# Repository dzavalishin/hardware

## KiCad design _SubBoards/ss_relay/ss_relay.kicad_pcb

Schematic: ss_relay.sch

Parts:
C1, C2, C3: 0,1; C_1206_HandSoldering
C4: 0,1 400v; C_Rect_L10.3mm_W5.0mm_P7.50mm_MKS4
D1, D7: MB6S; Diode_Bridge_TO-269AA
D2, D3: LED; LED_D3.0mm
D4: 7,5v 1500a; D_DO-201AD_P5.08mm_Vertical_KathodeUp
D5, D8: 5v6; D_1206
D6: RL206; D_DO-15_P5.08mm_Vertical_AnodeUp
F1: 0,5A; Fuseholder5x20_horiz_open_inline_Type-I
J1: DC Load; TerminalBlock_Pheonix_MPT-2.54mm_2pol
J2: AC220; TerminalBlock_Pheonix_MPT-2.54mm_2pol
P1: CONN_01X02; Pin_Header_Straight_1x02_Pitch2.54mm
Q1: IRF730; TO-220-3_Vertical
R1, R2: 560; R_1206_HandSoldering
R3, R4: 1k; R_1206_HandSoldering
R5, R6: 470k 1W; R_Axial_DIN0617_L17.0mm_D6.0mm_P20.32mm_Horizontal
R7: 56; R_Axial_DIN0617_L17.0mm_D6.0mm_P20.32mm_Horizontal
RV1: 14K391; RV_Disc_D21.5_W4.3_P10
U1: PC817; SOP-4_3.8x4.1mm_Pitch2.54mm

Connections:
unnamed: C1.1, D2.2, D8.1, R1.1, R4.2
unnamed: C1.2, D8.2, R2.2, R3.2, U1.2
unnamed: C2.1, D4.1, Q1.1 (G), R5.2, U1.4
unnamed: C2.2, D4.2, D7.2 (-), Q1.3 (S), U1.3
unnamed: C3.1, C4.1, D3.2, D5.1, D6.1, D7.1 (+), J1.2, R5.1
unnamed: C3.2, D3.1, D5.2, R6.1
unnamed: C4.2, R7.1
unnamed: D1.1 (+), R1.2
unnamed: D1.2 (-), R2.1
unnamed: D1.3, P1.1
unnamed: D1.4, P1.2
unnamed: D2.1, R3.1
unnamed: D6.2, J1.1, Q1.2 (D), R6.2, R7.2
unnamed: D7.3, J2.1, RV1.2
unnamed: D7.4, F1.2, RV1.1
unnamed: F1.1, J2.2
unnamed: R4.1, U1.1

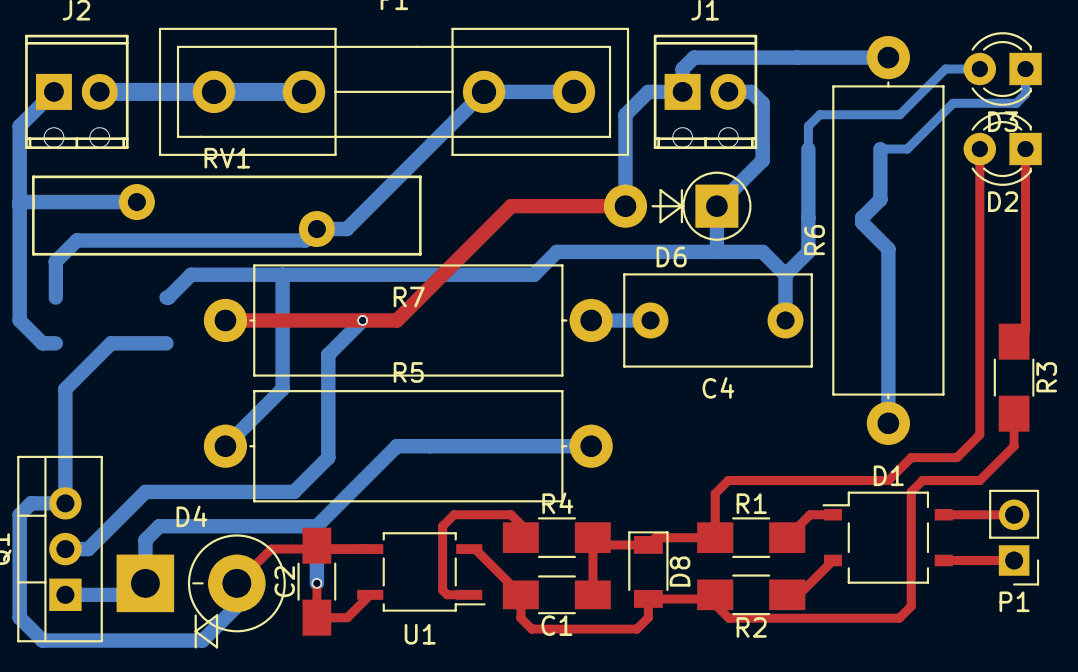
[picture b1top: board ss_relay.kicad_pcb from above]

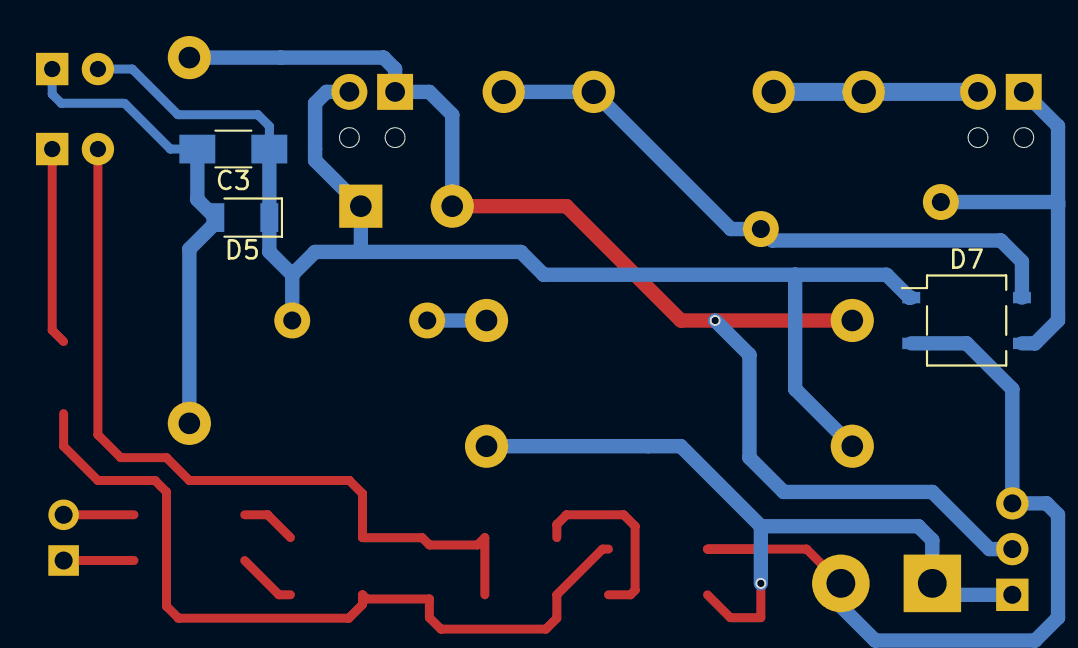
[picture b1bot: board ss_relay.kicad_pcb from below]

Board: 2 copper layers, 26 parts (3 on the bottom side), 17 nets.

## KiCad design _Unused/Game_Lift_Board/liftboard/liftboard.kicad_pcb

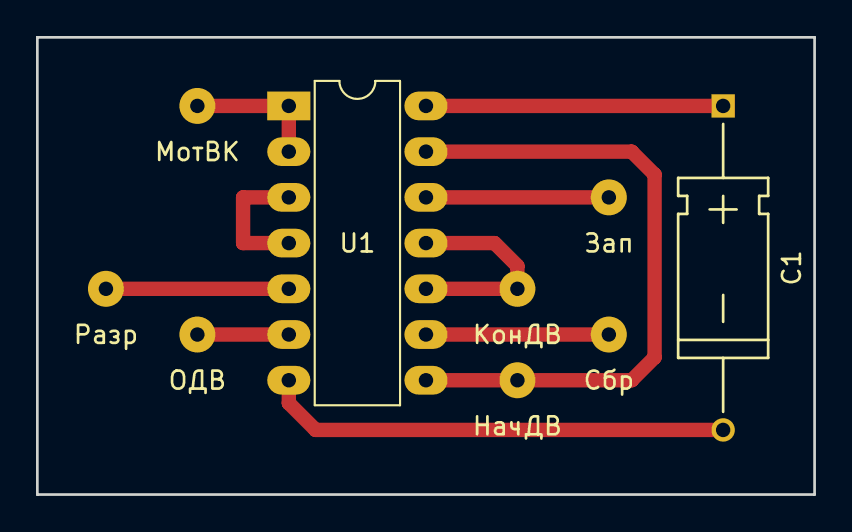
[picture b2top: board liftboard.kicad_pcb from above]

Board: 2 copper layers, 43.2 x 25.4 mm, 9 parts (0 on the bottom side), 10 nets.

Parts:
C1: C; C_Axial_D5_L11_P18
J1: МотВК; SolderWirePad_1x01_Drill0.8mm
J2: ОДВ; SolderWirePad_1x01_Drill0.8mm
J3: Разр; SolderWirePad_1x01_Drill0.8mm
J4: Зап; SolderWirePad_1x01_Drill0.8mm
J5: КонДВ; SolderWirePad_1x01_Drill0.8mm
J6: Сбр; SolderWirePad_1x01_Drill0.8mm
J7: НачДВ; SolderWirePad_1x01_Drill0.8mm
U1: 7400; DIP-14_W7.62mm_LongPads

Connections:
unnamed: C1.1, U1.14
unnamed: C1.2, U1.7
unnamed: J1.1, U1.1, U1.2
unnamed: J2.1, U1.6
unnamed: J3.1, U1.5
unnamed: J4.1, U1.12
unnamed: J5.1, U1.10, U1.11
unnamed: J6.1, U1.9
unnamed: J7.1, U1.8, U1.13
unnamed: U1.3, U1.4

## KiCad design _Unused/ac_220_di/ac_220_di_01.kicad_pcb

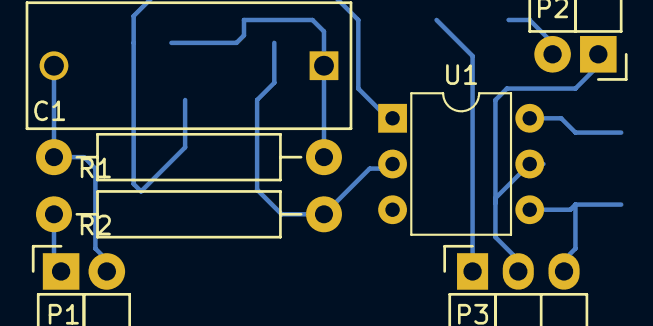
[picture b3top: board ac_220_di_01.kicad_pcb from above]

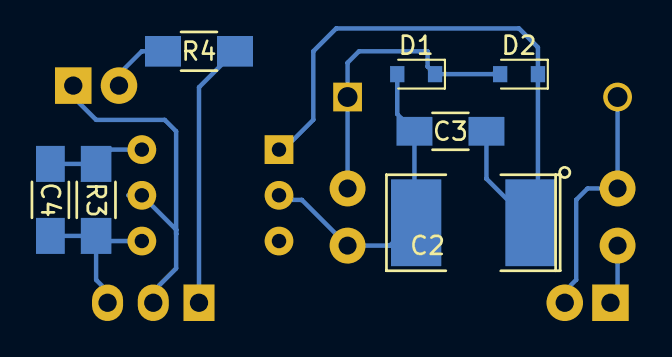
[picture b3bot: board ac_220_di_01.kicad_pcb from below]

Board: 2 copper layers, 14 parts (7 on the bottom side), 10 nets.

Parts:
C1: 0.15uF; C_Rect_L18_W7_P15
C2: 10,0; SMD-2112_Pol
C3: 0,1; C_1206_HandSoldering
C4: 100pf; C_1206_HandSoldering
D1, D2: 4448; D_0805
P1: In; Socket_Strip_Angled_1x02
P2: Led; Socket_Strip_Angled_1x02
P3: Out; Socket_Strip_Angled_1x03
R1: 3m; Resistor_Horizontal_RM15mm
R2: 10k 1W; Resistor_Horizontal_RM15mm
R3: 470k; R_1206_HandSoldering
R4: 4,7k (10ma) or 12k (2ma); R_1206_HandSoldering
U1: 4N35; DIP-6_W7.62mm

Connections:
unnamed: C1.1, D1.1, D2.2, R1.1
unnamed: C1.2, P1.2, R1.2
unnamed: C2.1, C3.1, D2.1, U1.1
unnamed: C2.2, C3.2, D1.2, R2.1, U1.2
unnamed: C4.1, R3.2, U1.6
unnamed: C4.2, P3.3, R3.1, U1.4
unnamed: P1.1, R2.2
unnamed: P2.1, P3.2, U1.5
unnamed: P2.2, R4.1
unnamed: P3.1, R4.2

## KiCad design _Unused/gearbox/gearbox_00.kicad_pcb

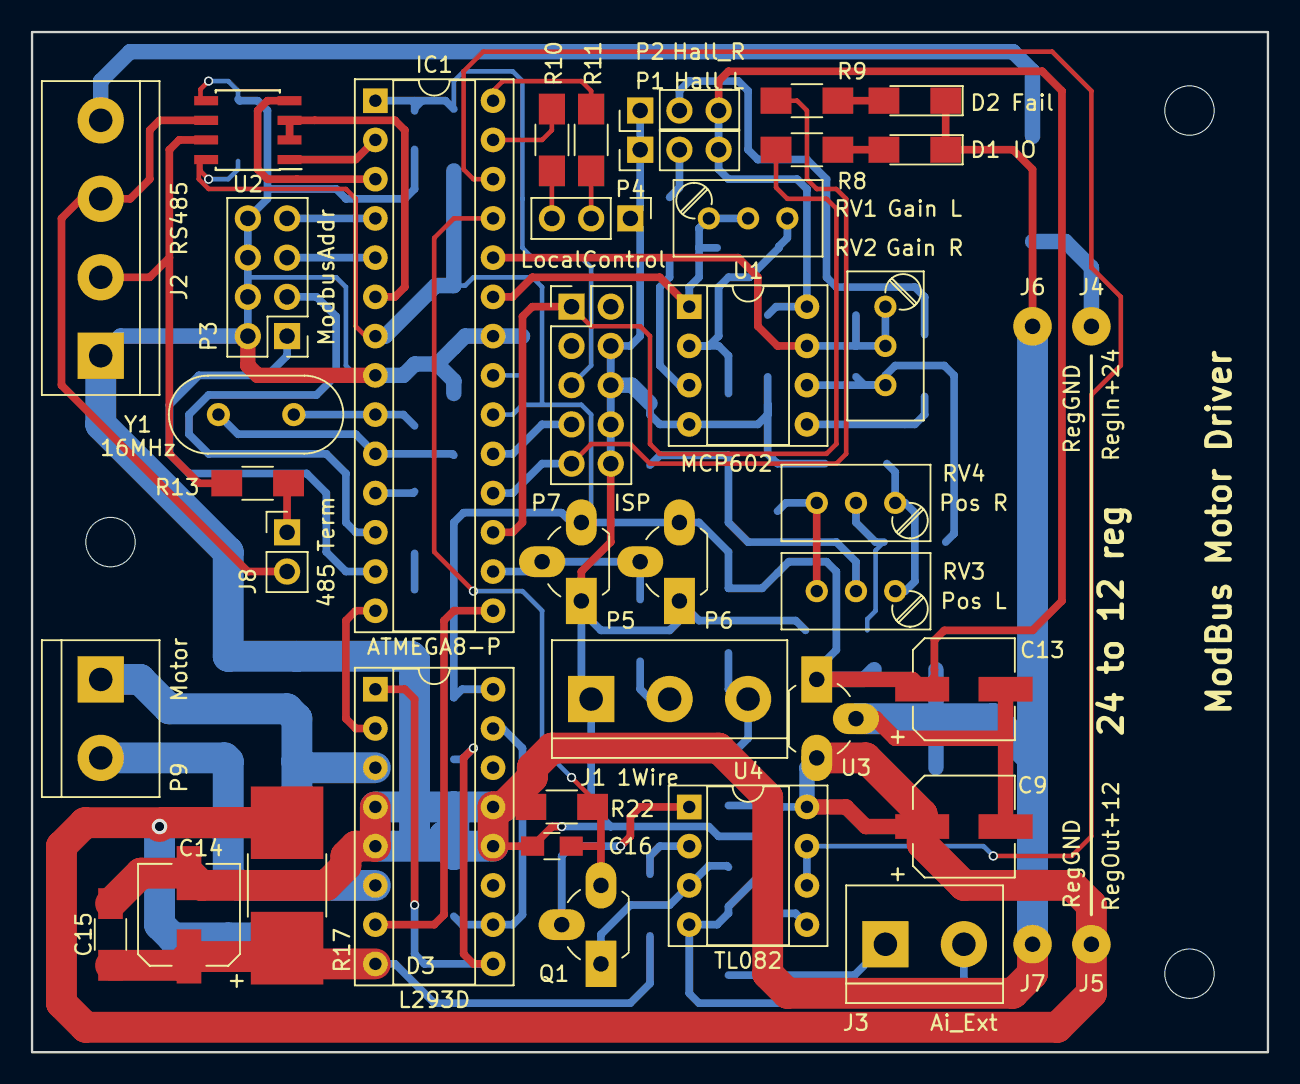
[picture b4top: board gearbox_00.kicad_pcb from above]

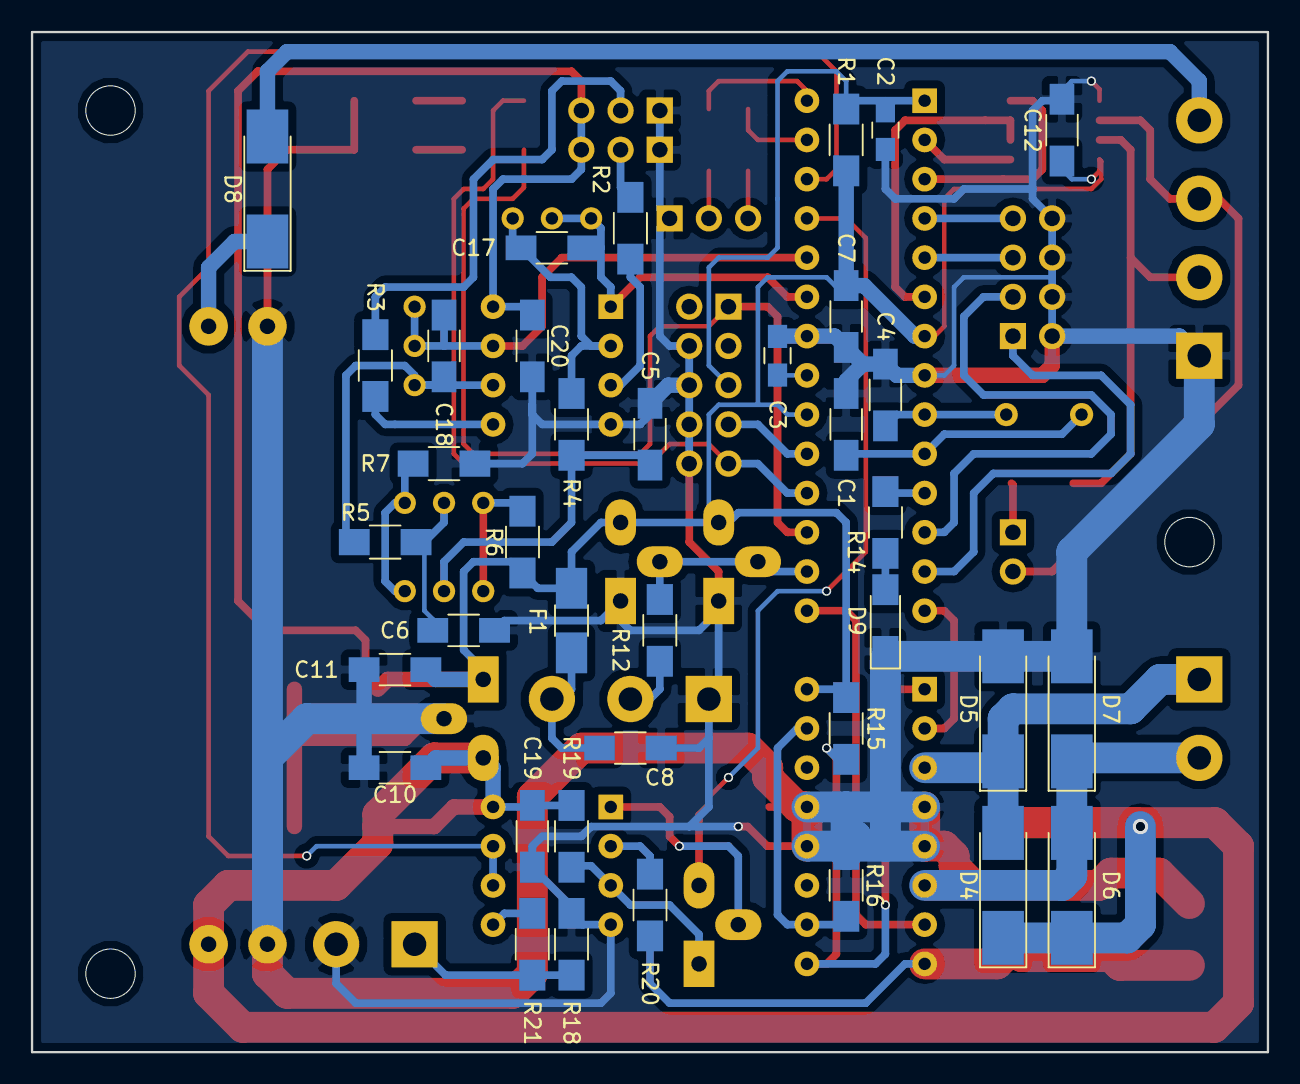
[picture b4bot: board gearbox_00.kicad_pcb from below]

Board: 2 copper layers, 80.0 x 66.0 mm, 82 parts (37 on the bottom side), 59 nets.

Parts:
C1, C4: 18pF; C_1206_HandSoldering
C2, C3, C16: 1,0; C_0805_HandSoldering
C5, C6, C7, C8, C10, C11, C12, C15, C19, C20: 0,1; C_1206_HandSoldering
C9: 220,0; CP_Elec_6.3x5.3
C13: 22,0; CP_Elec_6.3x5.3
C14: 47,0; CP_Elec_6.3x5.3
C17, C18: 0,01; C_1206_HandSoldering
D1: IO; LED_1206_HandSoldering
D2: Fail; LED_1206_HandSoldering
D3: L293D; DIP-16_W7.62mm_Socket
D4, D5, D6, D7, D8: SS34; D_MELF_Handsoldering
D9: Debug; LED_1206_HandSoldering
F1: 0,1a; Fuse_SMD1206_HandSoldering
IC1: ATMEGA8-P; DIP-28_W7.62mm_Socket
J1: 1Wire; TerminalBlock_bornier-3_P5.08mm
J2: RS485; TerminalBlock_bornier-4_P5.08mm
J3: Ai_Ext; TerminalBlock_bornier-2_P5.08mm
J4: RegIn+24; SolderWirePad_single_1mmDrill
J5: RegOut+12; SolderWirePad_single_1mmDrill
J6, J7: RegGND; SolderWirePad_single_1mmDrill
J8: 485 Term; Pin_Header_Straight_1x02_Pitch2.54mm
P1: Hall_L; Pin_Header_Straight_1x03_Pitch2.54mm
P2: Hall_R; Pin_Header_Straight_1x03_Pitch2.54mm
P3: ModbusAddr; Pin_Header_Straight_2x04_Pitch2.54mm
P4: LocalControl; Pin_Header_Straight_1x03_Pitch2.54mm
P5: DS2401; TO-92_Rugged
P6: DS18B20; TO-92_Rugged
P7: ISP; Pin_Header_Straight_2x05_Pitch2.54mm
P9: Motor; TerminalBlock_bornier-2_P5.08mm
Q1: 2N3904; TO-92_Rugged
R1, R6, R7, R10, R11, R21: 1k; R_1206_HandSoldering
R2, R3, R15, R16: 10k; R_1206_HandSoldering
R4, R5: 22k; R_1206_HandSoldering
R8, R9, R14: 2,2k; R_1206_HandSoldering
R12: 100; R_1206_HandSoldering
R13: 47; R_1206_HandSoldering
R17: 0,2; R_2816_HandSoldering
R18: 1M; R_1206_HandSoldering
R19, R20: 200; R_1206_HandSoldering
R22: 2k; R_1206_HandSoldering
RV1, RV2: 22k; Potentiometer_Trimmer_Bourns_3296W
RV3, RV4: 1k; Potentiometer_Trimmer_Bourns_3296W
U1: MCP602; DIP-8_W7.62mm_Socket
U2: MAX485; SOIC-8_3.9x4.9mm_Pitch1.27mm
U3: LM78L05ACZ; TO-92_Rugged
U4: TL082; DIP-8_W7.62mm_Socket
Y1: 16MHz; Crystal_HC49-U_Vertical
hole: MountingHole_3.2mm_M3
hole#2, hole#3: MountingHole_3.2mm_M3

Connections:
+5V: C7.1, C11.2, C12.1, C13.1, C20.1, D3.16, F1.2, IC1.7, IC1.20, P1.3, P2.3, P5.3, P6.3, R1.1, R6.1, R15.2, U1.8, U2.8, U3.1
+12V: C9.1, C10.1, C19.1, D4.1, D6.1, J5.1, R17.1, R19.2, U3.3, U4.8
+24V: D8.1, J4.1
/1Wire: IC1.16, P5.2, P6.2, R12.2
/Ai_Ext: IC1.26, U4.6, U4.7
/Ai_Hall_A: C17.1, IC1.23, RV1.1, RV1.2, U1.1
/Ai_Hall_B: C18.1, IC1.24, RV2.1, RV2.2, U1.7
/Ai_I_Sense: C16.1, IC1.25, Q1.3, R22.1
/Fail_Led: IC1.18, P7.9, R9.2
/IO_Led: IC1.17, P7.1, R8.2
/LocalClose: IC1.28, R11.2
/LocalOpen: IC1.27, R10.2
/OutA: D3.2, IC1.14
/OutB: D3.7, IC1.15
/Reset: C2.1, IC1.1, P7.5, R1.2
/Rx: IC1.2, U2.1
/SCK: IC1.19, P7.7
/Tx: IC1.3, U2.4
/TxE: IC1.6, U2.2, U2.3
GND: C1.2, C2.2, C3.2, C4.2, C5.2, C6.2, C7.2, C8.2, C9.2, C10.2, C11.1, C12.2, C13.2, C14.2, C15.2, C16.2, C19.2, C20.2, D1.1, D2.1, D3.4, D3.5, D3.12, D3.13, D5.2, D7.2, D9.1, IC1.8, IC1.22, J1.1, J2.1, J3.2, J6.1, J7.1, P1.1, P2.1, P3.2, P3.4, P3.6, P3.8, P4.1, P5.1, P6.1, P7.4, P7.6, P7.8, P7.10, R7.2, R16.1, R18.1, R22.2, U1.4, U2.5, U3.2, U4.4
unnamed: C1.1, IC1.10, Y1.1
unnamed: C3.1, IC1.21
unnamed: C4.1, IC1.9, Y1.2
unnamed: C5.1, R4.2, RV3.2
unnamed: C6.1, R5.2, RV4.2
unnamed: C8.1, F1.1, J1.3
unnamed: C14.1, C15.1, D3.8, R17.2, R20.2
unnamed: C17.2, R4.1, RV1.3, U1.2
unnamed: C18.2, R5.1, RV2.3, U1.6
unnamed: D1.2, R8.1
unnamed: D2.2, R9.1
unnamed: D3.1, D3.9, R15.1
unnamed: D3.3, D4.2, D5.1, P9.1
unnamed: D3.6, D6.2, D7.1, P9.2
unnamed: D3.10, D3.15, R16.2
unnamed: D8.2, J2.4
unnamed: D9.2, R14.1
unnamed: IC1.4, P3.7
unnamed: IC1.5, P3.5
unnamed: IC1.11, R14.2
unnamed: IC1.12, P3.3
unnamed: IC1.13, P3.1
unnamed: J1.2, R12.1
unnamed: J2.2, R13.2, U2.7
unnamed: J2.3, J8.2, U2.6
unnamed: J3.1, R18.2, R21.2
unnamed: J8.1, R13.1
unnamed: P1.2, R2.2
unnamed: P2.2, R3.2
unnamed: P4.2, R11.1
unnamed: P4.3, R10.1
unnamed: Q1.1, R19.1, U4.3
unnamed: Q1.2, U4.1
unnamed: R2.1, U1.3
unnamed: R3.1, U1.5
unnamed: R6.2, RV3.3, RV4.3
unnamed: R7.1, RV3.1, RV4.1
unnamed: R20.1, U4.2
unnamed: R21.1, U4.5

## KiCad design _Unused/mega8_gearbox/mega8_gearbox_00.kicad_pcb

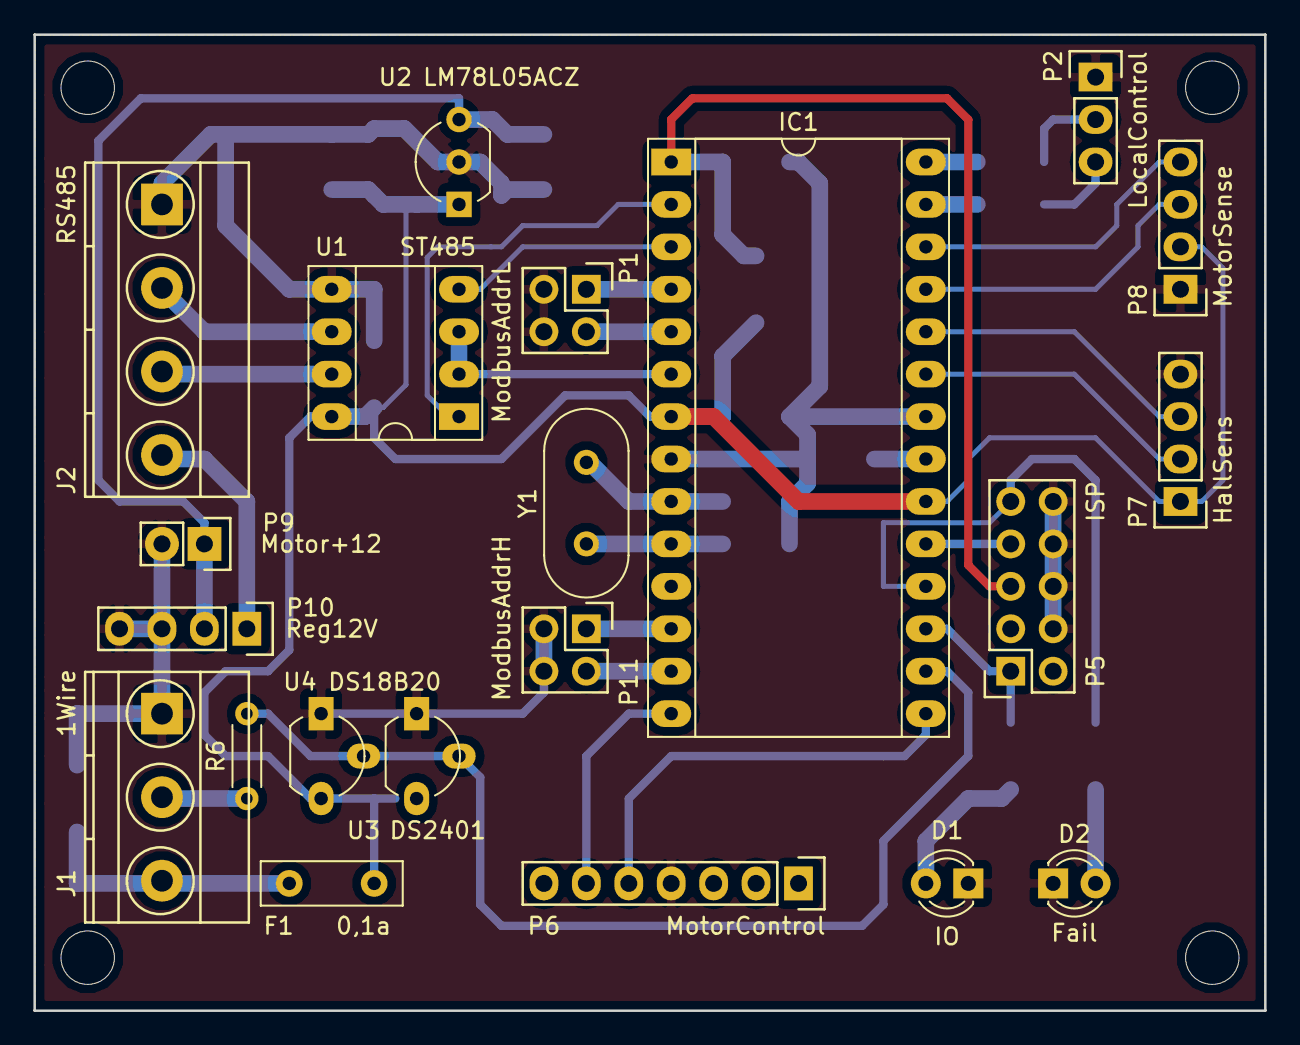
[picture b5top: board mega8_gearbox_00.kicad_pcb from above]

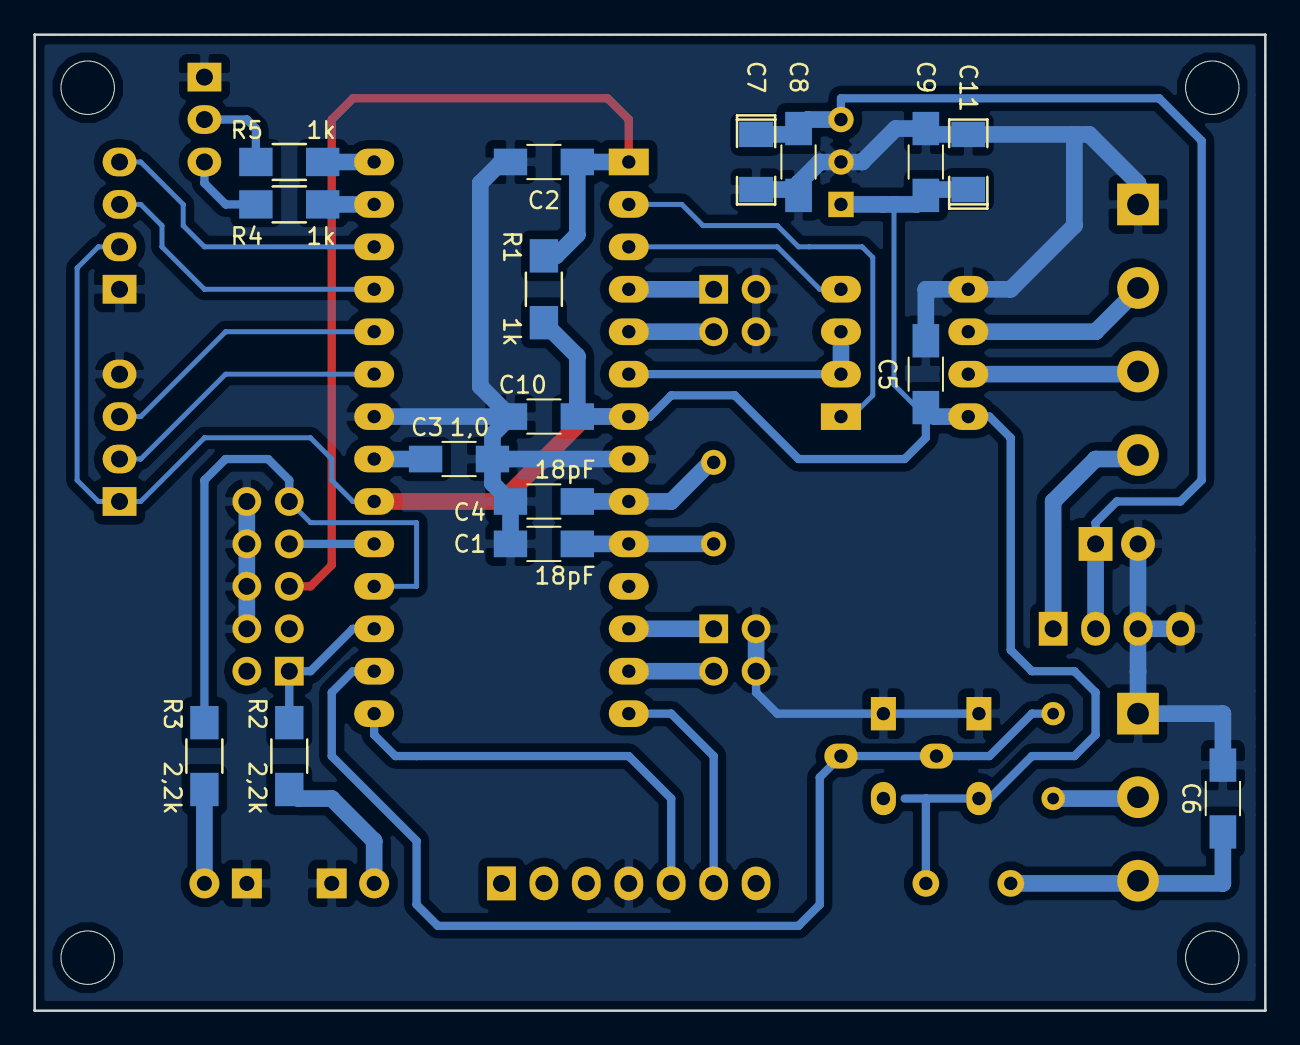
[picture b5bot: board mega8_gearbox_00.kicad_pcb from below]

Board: 2 copper layers, 73.7 x 58.4 mm, 41 parts (16 on the bottom side), 35 nets.

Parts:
C1, C4: 18pF; C_1206_HandSoldering
C2, C3: 1,0; C_1206_HandSoldering
C5, C6, C8, C9, C10: 0,1; C_1206_HandSoldering
C7, C11: 10,0; SMD-1206_Pol
D1: IO; LED_D3.0mm
D2: Fail; LED_D3.0mm
F1: 0,1a; R_Box_L8.4mm_W2.5mm_P5.08mm
IC1: ATMEGA8-P; DIP-28_W15.24mm_Socket_LongPads
J1: 1Wire; TerminalBlock_Pheonix_MKDS1.5-3pol
J2: RS485; TerminalBlock_Pheonix_MKDS1.5-4pol
P1: ModbusAddrL; Socket_Strip_Straight_2x02
P2: LocalControl; Socket_Strip_Straight_1x03
P5: ISP; Socket_Strip_Straight_2x05
P6: MotorControl; Socket_Strip_Straight_1x07
P7: HallSens; Socket_Strip_Straight_1x04
P8: MotorSense; Socket_Strip_Straight_1x04
P9: Motor+12; Socket_Strip_Straight_1x02
P10: Reg12V; Socket_Strip_Straight_1x04
P11: ModbusAddrH; Socket_Strip_Straight_2x02
R1, R4, R5: 1k; R_1206_HandSoldering
R2, R3: 2,2k; R_1206_HandSoldering
R6: 100; R_Axial_DIN0204_L3.6mm_D1.6mm_P5.08mm_Horizontal
U1: ST485; DIP-8_W7.62mm_Socket_LongPads
U2: LM78L05ACZ; TO-92_Inline_Wide
U3: DS2401; TO-92_Molded_Wide_Oval
U4: DS18B20; TO-92_Molded_Wide_Oval
Y1: 16MHz; Crystal_HC49-U_Vertical
hole: MountingHole_3.2mm_M3
hole#2, hole#3, hole#4: MountingHole_3.2mm_M3

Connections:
+5V: C5.1, C9.2, C10.1, C11.1, F1.2, IC1.7, IC1.20, P7.1, P8.2, R1.1, U1.8, U2.1, U4.3
+12V: C7.1, C8.1, P9.1, P10.2, U2.3
+24V: J2.4, P10.1
/1Wire: IC1.16, R6.2, U3.2, U4.2
/Ai_Ext: IC1.26, P8.4
/Ai_Hall_A: IC1.23, P7.2
/Ai_Hall_B: IC1.24, P7.3
/Ai_I_Sense: IC1.25, P8.3
/Fail_Led: IC1.18, P5.9, R3.2
/IO_Led: IC1.17, P5.1, R2.2
/LocalClose: IC1.28, R5.2
/LocalOpen: IC1.27, R4.2
/OutA: IC1.14, P6.6
/OutB: IC1.15, P6.5
/Reset: C2.1, IC1.1, P5.5, R1.2
/Rx: IC1.2, U1.1
/SCK: IC1.19, P5.7
/Tx: IC1.3, U1.4
/TxE: IC1.6, U1.2, U1.3
GND: C1.2, C2.2, C3.2, C4.2, C5.2, C6.2, C7.2, C8.2, C9.1, C10.2, C11.2, D1.1, D2.1, IC1.8, IC1.22, J1.1, J2.1, P1.2, P1.4, P2.1, P5.4, P5.6, P5.8, P5.10, P6.4, P7.4, P8.1, P9.2, P10.3, P10.4, P11.2, P11.4, U1.5, U2.2, U3.1, U4.1
unnamed: C1.1, IC1.10, Y1.1
unnamed: C3.1, IC1.21
unnamed: C4.1, IC1.9, Y1.2
unnamed: C6.1, F1.1, J1.3
unnamed: D1.2, R2.1
unnamed: D2.2, R3.1
unnamed: IC1.4, P1.1
unnamed: IC1.5, P1.3
unnamed: IC1.12, P11.1
unnamed: IC1.13, P11.3
unnamed: J1.2, R6.1
unnamed: J2.2, U1.6
unnamed: J2.3, U1.7
unnamed: P2.2, R5.1
unnamed: P2.3, R4.1

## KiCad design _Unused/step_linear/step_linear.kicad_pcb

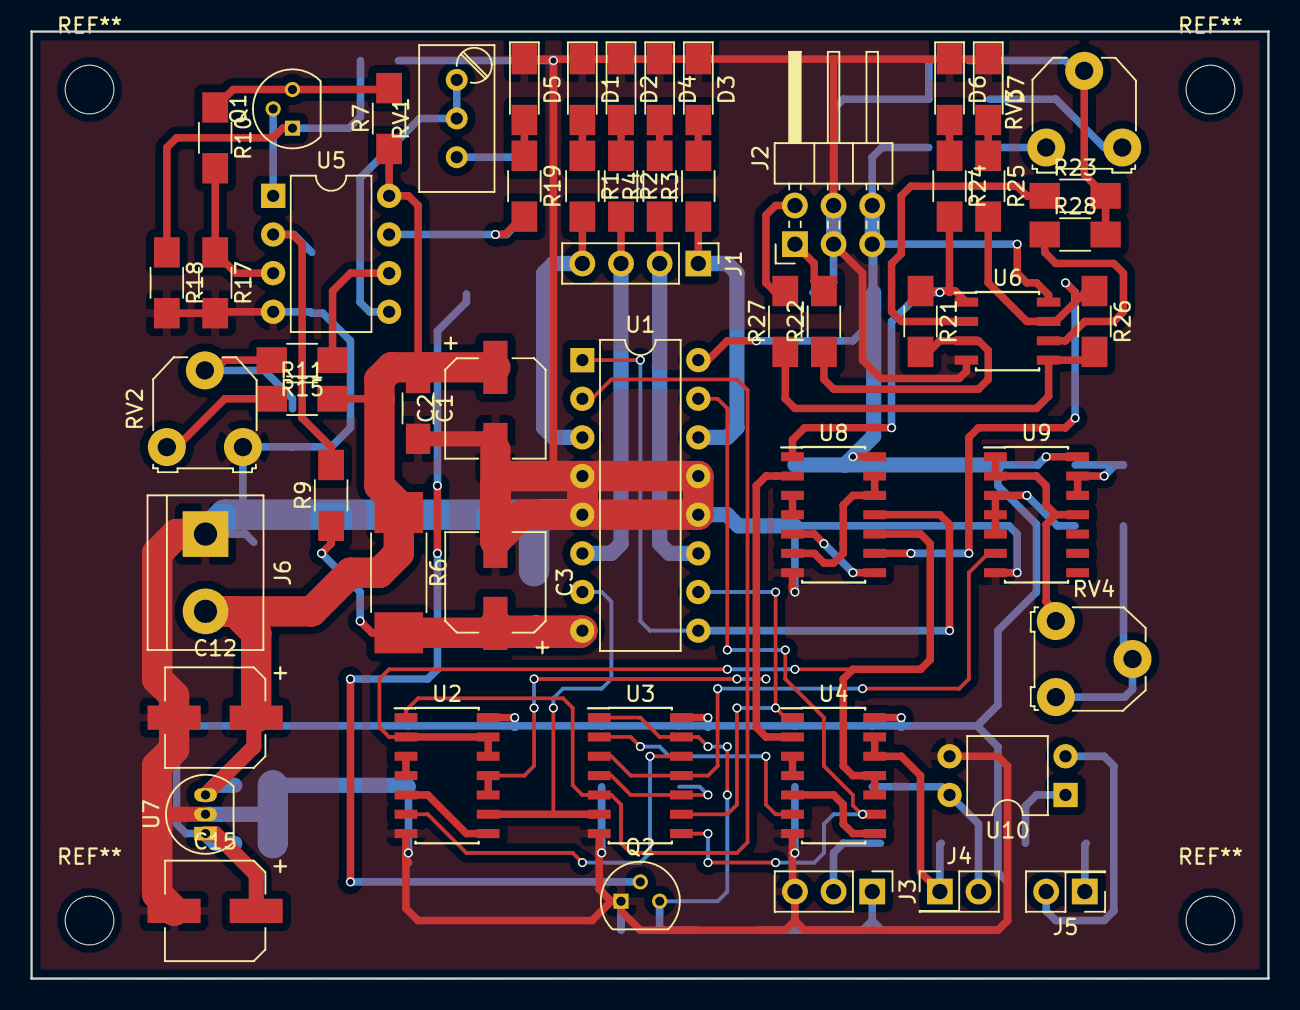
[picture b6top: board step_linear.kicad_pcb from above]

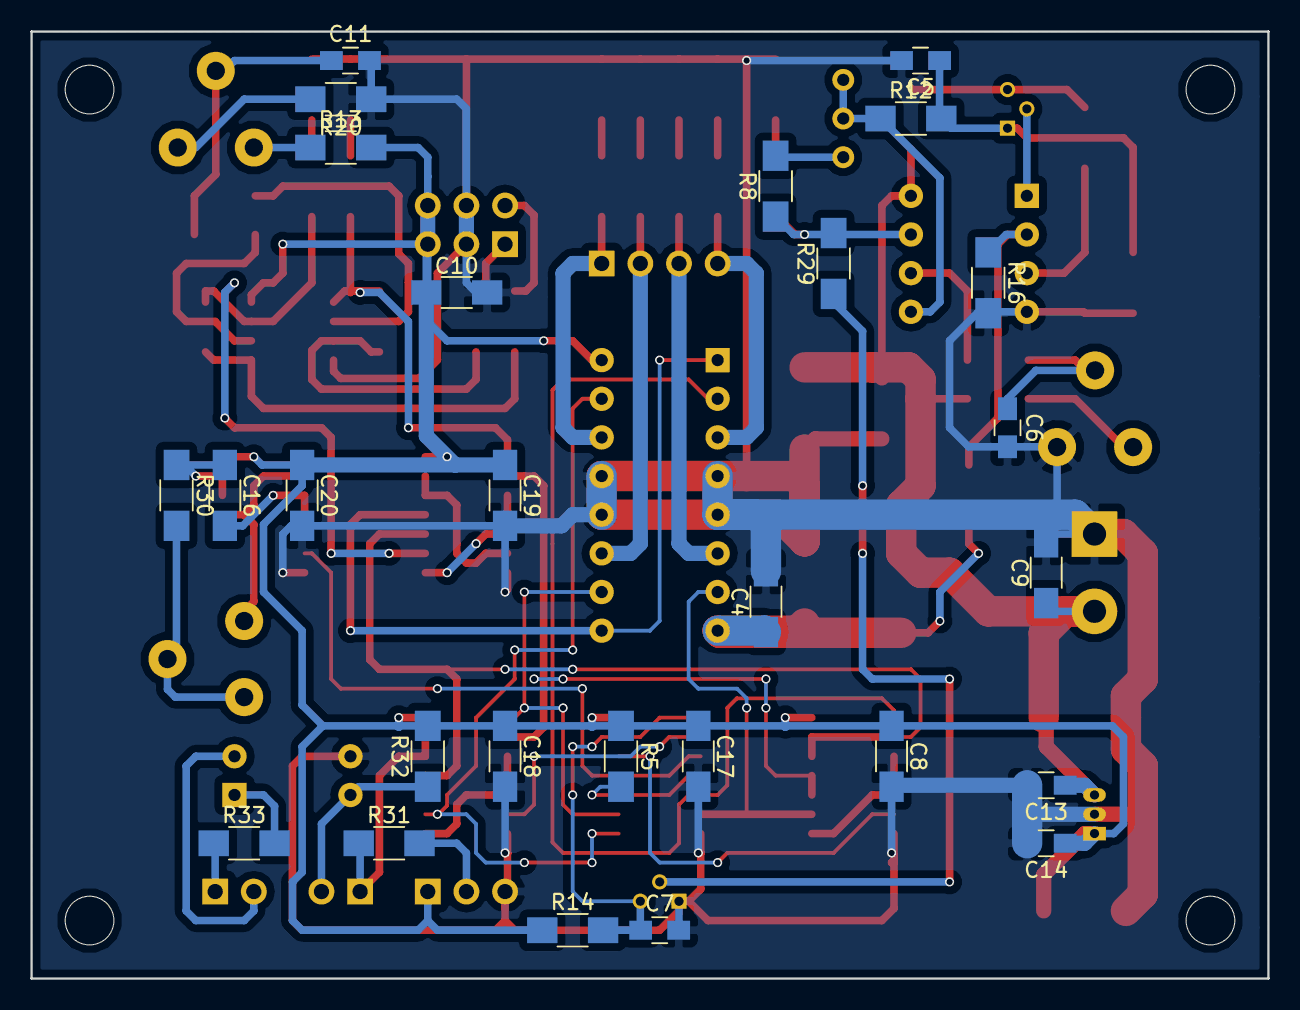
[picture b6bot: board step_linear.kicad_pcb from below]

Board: 2 copper layers, 81.3 x 62.2 mm, 82 parts (27 on the bottom side), 67 nets.

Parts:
C1, C4, C8, C9, C10, C17, C18, C19, C20: 0,1; C_1206_HandSoldering
C2, C3, C12: 47,0; CP_Elec_6.3x5.3
C5, C6, C7, C11: 1,0; C_0805_HandSoldering
C13, C14: 0,33; C_0805_HandSoldering
C15: 100,0; CP_Elec_6.3x5.7
C16: 0,15; C_1206_HandSoldering
D1, D2, D3, D4, D5, D6, D7: LED; LED_1206_HandSoldering
J1: Motor; Pin_Header_Straight_1x04_Pitch2.54mm
J2: Hall; Pin_Header_Angled_2x03_Pitch2.54mm
J3: Direction; Pin_Header_Straight_1x03_Pitch2.54mm
J4: Opto; Pin_Header_Straight_2x01_Pitch2.54mm
J5: Dir; Pin_Header_Straight_2x01_Pitch2.54mm
J6: +12; TerminalBlock_bornier-2_P5.08mm
Q1, Q2: 2N3904; TO-92_Molded_Narrow
R1, R2, R3, R4, R19, R24, R25: 560; R_1206_HandSoldering
R5, R9, R10, R12, R14, R15, R16, R17, R29: 10k; R_1206_HandSoldering
R6: 0,2 2W 1%; R_2512_HandSoldering
R7: 200 1%; R_1206_HandSoldering
R8: 1,5m; R_1206_HandSoldering
R11: 9,1k; R_1206_HandSoldering
R13, R20, R22, R23, R27, R28, R32, R33: 1k; R_1206_HandSoldering
R18: 2k 1%; R_1206_HandSoldering
R21, R26: 220k; R_1206_HandSoldering
R30: 3,3k; R_1206_HandSoldering
R31: 120; R_1206_HandSoldering
RV1: 1m; Potentiometer_Trimmer_Bourns_3296W
RV2, RV3, RV4: 1k; Potentiometer_Triwood_RM-065
U1: L293D; DIP-16_W7.62mm
U2, U4, U8, U9: 74HC00; SOIC-14_3.9x8.7mm_Pitch1.27mm
U3: 74HC74; SOIC-14_3.9x8.7mm_Pitch1.27mm
U5: TL082; DIP-8_W7.62mm
U6: LM2904; SOIC-8_3.9x4.9mm_Pitch1.27mm
U7: L78L05; TO-92_Inline_Narrow_Oval
U10: PC817; DIP-4_W7.62mm

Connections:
+5V: C8.1, C10.1, C14.1, C15.1, C17.1, C18.1, C19.1, C20.1, J2.5, J2.6, J3.1, R5.1, R13.2, R14.1, R32.2, U1.16, U2.14, U3.14, U4.14, U6.8, U7.1, U8.14, U9.14
+12V: C1.1, C2.1, C9.1, C12.1, C13.1, J6.2, R6.1, R7.1, R11.2, U5.8, U7.3
/CurrentMeter/Sense: C5.1, Q1.1, R12.2, R18.1
/Direction: U2.2, U2.12, U2.13, U4.10, U4.11, U8.10
/HallSensors/S1: R21.1, R24.2, U6.1, U8.1
/HallSensors/S2: R25.2, R26.1, U6.7, U8.9
/MPower: C3.1, C4.1, R6.2, R9.1, U1.8
/Overload: R8.1, R19.2, R29.2, U5.7
/Run: U1.1, U1.9, U8.11
/Step: U3.3, U3.11, U9.6
/~Direction: U2.10, U2.11, U4.2, U8.2
GND: C1.2, C2.2, C3.2, C4.2, C5.2, C6.2, C7.2, C8.2, C9.2, C10.2, C11.2, C12.2, C13.2, C14.2, C15.2, C17.2, C18.2, C19.2, C20.2, D1.1, D2.1, D3.1, D4.1, D5.1, D6.1, D7.1, J2.3, J2.4, J3.3, J6.1, Q2.1, R16.2, R17.2, R18.2, R20.1, RV2.3, U1.4, U1.5, U1.12, U1.13, U2.7, U3.7, U4.7, U5.4, U6.4, U7.2, U8.7, U9.7, U10.3
unnamed: C6.1, R15.2, RV2.2
unnamed: C7.1, Q2.3, R14.2, U3.1, U3.13
unnamed: C11.1, R23.2, R28.2, RV3.2
unnamed: C16.1, R30.1, U9.12, U9.13
unnamed: C16.2, U9.3, U9.4, U9.5
unnamed: D1.2, R1.1
unnamed: D2.2, R2.1
unnamed: D3.2, R3.2
unnamed: D4.2, R4.2
unnamed: D5.2, R19.1
unnamed: D6.2, R24.1
unnamed: D7.2, R25.1
unnamed: J1.1, R3.1, U1.14
unnamed: J1.2, R4.1, U1.11
unnamed: J1.3, R2.2, U1.6
unnamed: J1.4, R1.2, U1.3
unnamed: J2.1, R22.2
unnamed: J2.2, R27.2
unnamed: J3.2, R31.2
unnamed: J4.1, R31.1, U4.12, U4.13
unnamed: J4.2, R32.1, U10.4
unnamed: J5.1, R33.1
unnamed: J5.2, U10.2
unnamed: Q1.2, U5.1
unnamed: Q1.3, R7.2, R10.1
unnamed: Q2.2, R29.1
unnamed: R5.2, U3.4, U3.10
unnamed: R8.2, RV1.3
unnamed: R10.2, R17.1, U5.3
unnamed: R11.1, RV2.1
unnamed: R12.1, RV1.1, RV1.2, U5.5
unnamed: R13.1, RV3.1
unnamed: R15.1, U5.6
unnamed: R9.2, R16.1, U5.2
unnamed: R20.2, RV3.3
unnamed: R21.2, R22.1, U6.3
unnamed: R23.1, U6.2
unnamed: R26.2, R27.1, U6.5
unnamed: R28.1, U6.6
unnamed: R30.2, RV4.2, RV4.3
unnamed: R33.2, U10.1
unnamed: RV4.1, U9.1, U9.2, U9.11
unnamed: U1.2, U2.1, U3.5
unnamed: U1.7, U2.9, U3.6
unnamed: U1.10, U3.9, U4.1
unnamed: U1.15, U3.8, U4.9
unnamed: U2.3, U2.4
unnamed: U2.5, U2.8
unnamed: U2.6, U3.12
unnamed: U3.2, U4.6
unnamed: U4.3, U4.4
unnamed: U4.5, U4.8
unnamed: U8.3, U8.4
unnamed: U8.5, U8.8
unnamed: U8.6, U8.12, U8.13
